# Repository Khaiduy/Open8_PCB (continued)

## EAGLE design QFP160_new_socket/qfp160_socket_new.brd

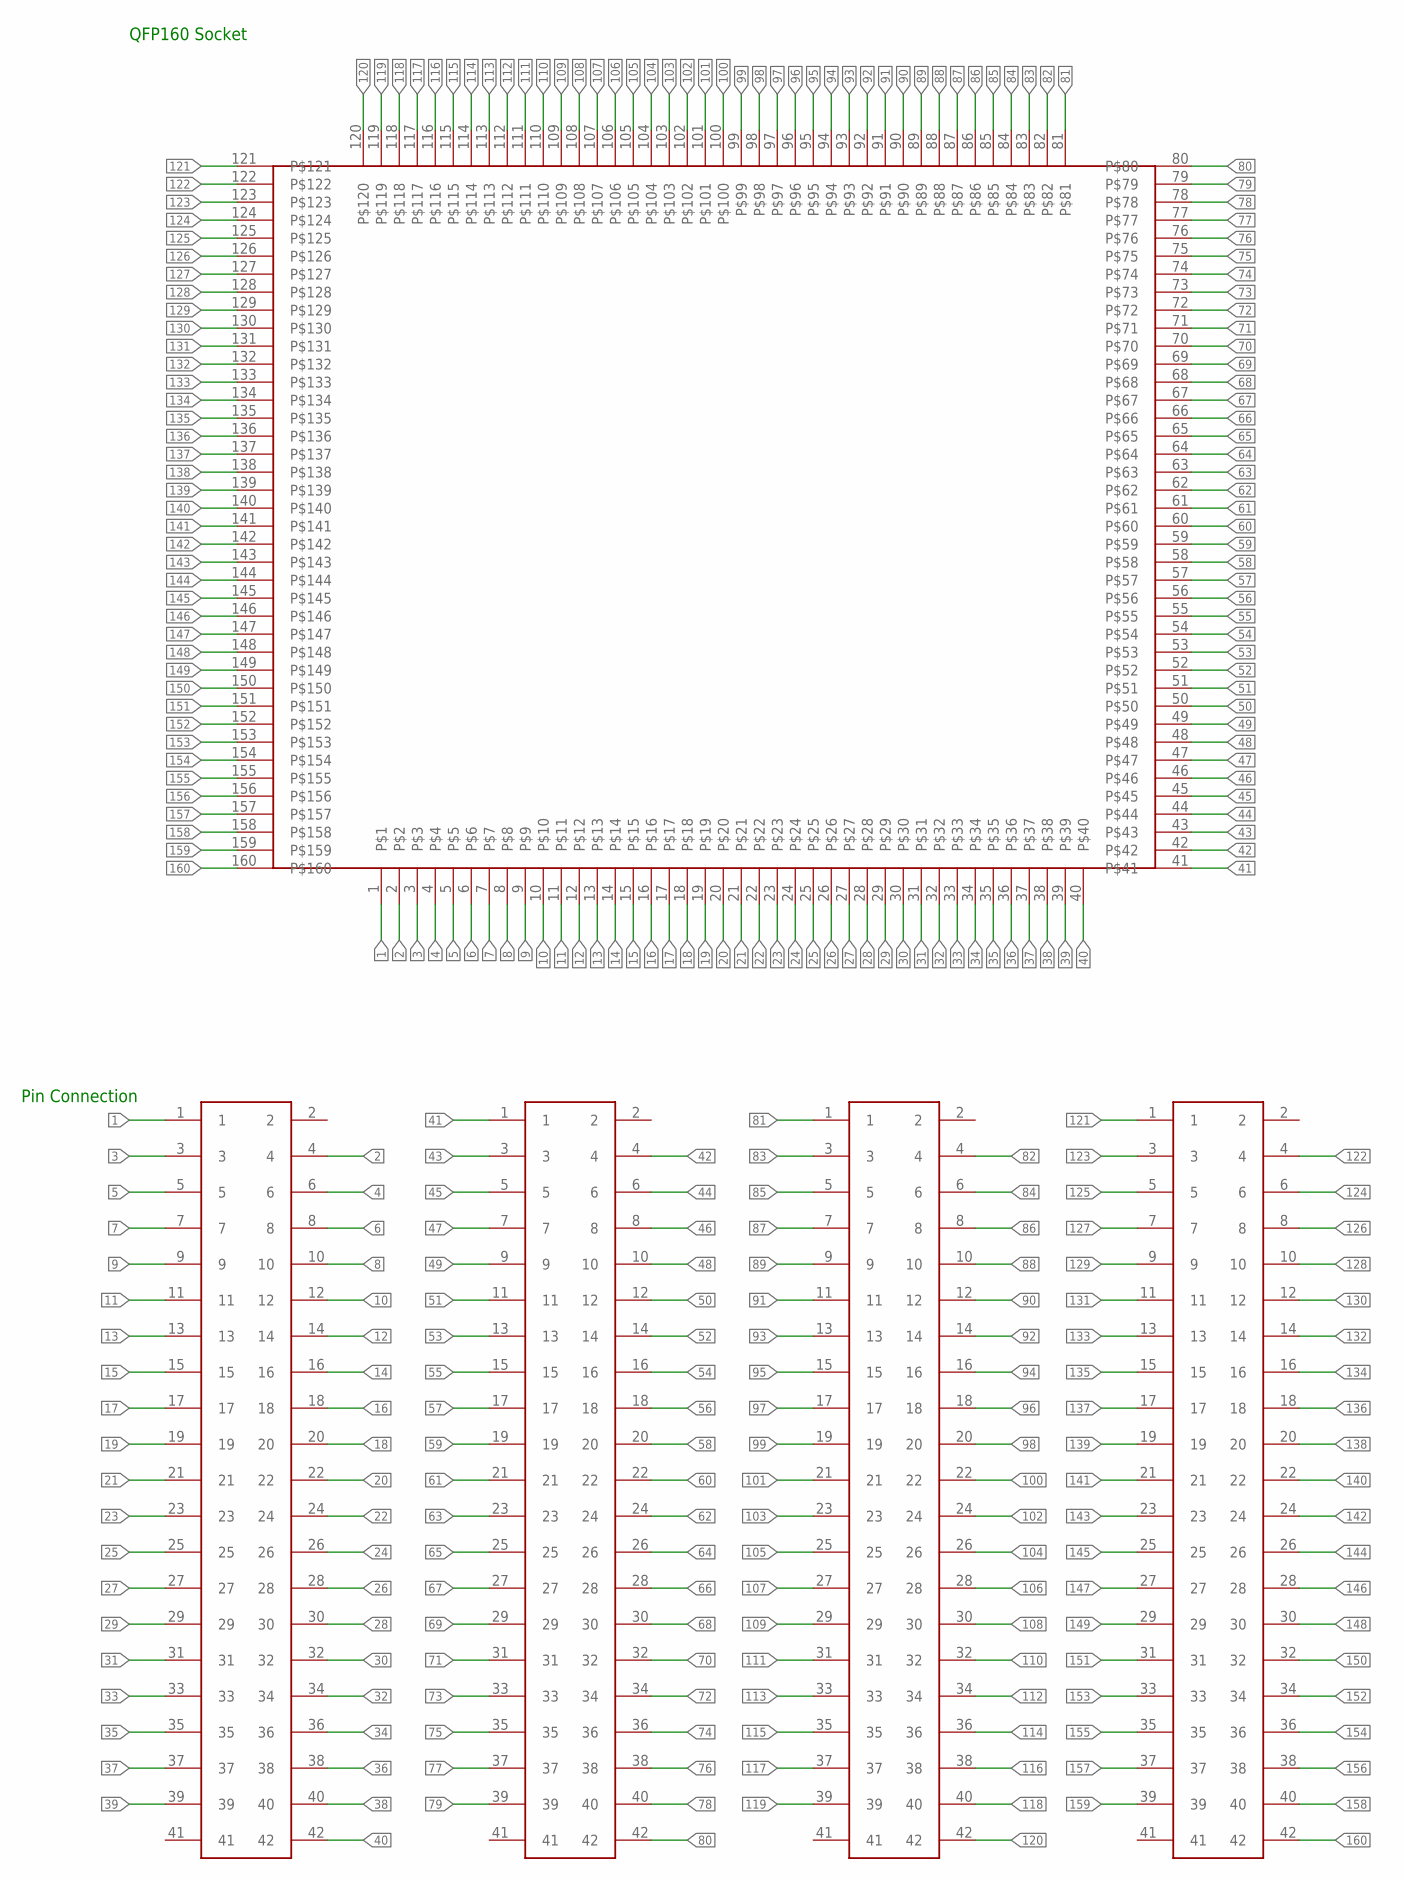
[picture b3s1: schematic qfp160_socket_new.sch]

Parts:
U$1, U$2, U$3, U$4: 2X41_HEADER
U$5: QFP160_SOCKET

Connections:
1: U$1.1, U$5.1
2: U$1.4, U$5.2
3: U$1.3, U$5.3
4: U$1.6, U$5.4
5: U$1.5, U$5.5
6: U$1.8, U$5.6
7: U$1.7, U$5.7
8: U$1.10, U$5.8
9: U$1.9, U$5.9
10: U$1.12, U$5.10
11: U$1.11, U$5.11
12: U$1.14, U$5.12
13: U$1.13, U$5.13
14: U$1.16, U$5.14
15: U$1.15, U$5.15
16: U$1.18, U$5.16
17: U$1.17, U$5.17
18: U$1.20, U$5.18
19: U$1.19, U$5.19
20: U$1.22, U$5.20
21: U$1.21, U$5.21
22: U$1.24, U$5.22
23: U$1.23, U$5.23
24: U$1.26, U$5.24
25: U$1.25, U$5.25
26: U$1.28, U$5.26
27: U$1.27, U$5.27
28: U$1.30, U$5.28
29: U$1.29, U$5.29
30: U$1.32, U$5.30
31: U$1.31, U$5.31
32: U$1.34, U$5.32
33: U$1.33, U$5.33
34: U$1.36, U$5.34
35: U$1.35, U$5.35
36: U$1.38, U$5.36
37: U$1.37, U$5.37
38: U$1.40, U$5.38
39: U$1.39, U$5.39
40: U$1.42, U$5.40
41: U$2.1, U$5.41
42: U$2.4, U$5.42
43: U$2.3, U$5.43
44: U$2.6, U$5.44
45: U$2.5, U$5.45
46: U$2.8, U$5.46
47: U$2.7, U$5.47
48: U$2.10, U$5.48
49: U$2.9, U$5.49
50: U$2.12, U$5.50
51: U$2.11, U$5.51
52: U$2.14, U$5.52
53: U$2.13, U$5.53
54: U$2.16, U$5.54
55: U$2.15, U$5.55
56: U$2.18, U$5.56
57: U$2.17, U$5.57
58: U$2.20, U$5.58
59: U$2.19, U$5.59
60: U$2.22, U$5.60
61: U$2.21, U$5.61
62: U$2.24, U$5.62
63: U$2.23, U$5.63
64: U$2.26, U$5.64
65: U$2.25, U$5.65
66: U$2.28, U$5.66
67: U$2.27, U$5.67
68: U$2.30, U$5.68
69: U$2.29, U$5.69
70: U$2.32, U$5.70
71: U$2.31, U$5.71
72: U$2.34, U$5.72
73: U$2.33, U$5.73
74: U$2.36, U$5.74
75: U$2.35, U$5.75
76: U$2.38, U$5.76
77: U$2.37, U$5.77
78: U$2.40, U$5.78
79: U$2.39, U$5.79
80: U$2.42, U$5.80
81: U$3.1, U$5.81
82: U$3.4, U$5.82
83: U$3.3, U$5.83
84: U$3.6, U$5.84
85: U$3.5, U$5.85
86: U$3.8, U$5.86
87: U$3.7, U$5.87
88: U$3.10, U$5.88
89: U$3.9, U$5.89
90: U$3.12, U$5.90
91: U$3.11, U$5.91
92: U$3.14, U$5.92
93: U$3.13, U$5.93
94: U$3.16, U$5.94
95: U$3.15, U$5.95
96: U$3.18, U$5.96
97: U$3.17, U$5.97
98: U$3.20, U$5.98
99: U$3.19, U$5.99
100: U$3.22, U$5.100
101: U$3.21, U$5.101
102: U$3.24, U$5.102
103: U$3.23, U$5.103
104: U$3.26, U$5.104
105: U$3.25, U$5.105
106: U$3.28, U$5.106
107: U$3.27, U$5.107
108: U$3.30, U$5.108
109: U$3.29, U$5.109
110: U$3.32, U$5.110
111: U$3.31, U$5.111
112: U$3.34, U$5.112
113: U$3.33, U$5.113
114: U$3.36, U$5.114
115: U$3.35, U$5.115
116: U$3.38, U$5.116
117: U$3.37, U$5.117
118: U$3.40, U$5.118
119: U$3.39, U$5.119
120: U$3.42, U$5.120
121: U$4.1, U$5.121
122: U$4.4, U$5.122
123: U$4.3, U$5.123
124: U$4.6, U$5.124
125: U$4.5, U$5.125
126: U$4.8, U$5.126
127: U$4.7, U$5.127
128: U$4.10, U$5.128
129: U$4.9, U$5.129
130: U$4.12, U$5.130
131: U$4.11, U$5.131
132: U$4.14, U$5.132
133: U$4.13, U$5.133
134: U$4.16, U$5.134
135: U$4.15, U$5.135
136: U$4.18, U$5.136
137: U$4.17, U$5.137
138: U$4.20, U$5.138
139: U$4.19, U$5.139
140: U$4.22, U$5.140
141: U$4.21, U$5.141
142: U$4.24, U$5.142
143: U$4.23, U$5.143
144: U$4.26, U$5.144
145: U$4.25, U$5.145
146: U$4.28, U$5.146
147: U$4.27, U$5.147
148: U$4.30, U$5.148
149: U$4.29, U$5.149
150: U$4.32, U$5.150
151: U$4.31, U$5.151
152: U$4.34, U$5.152
153: U$4.33, U$5.153
154: U$4.36, U$5.154
155: U$4.35, U$5.155
156: U$4.38, U$5.156
157: U$4.37, U$5.157
158: U$4.40, U$5.158
159: U$4.39, U$5.159
160: U$4.42, U$5.160

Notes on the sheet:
QFP160 Socket
Pin Connection

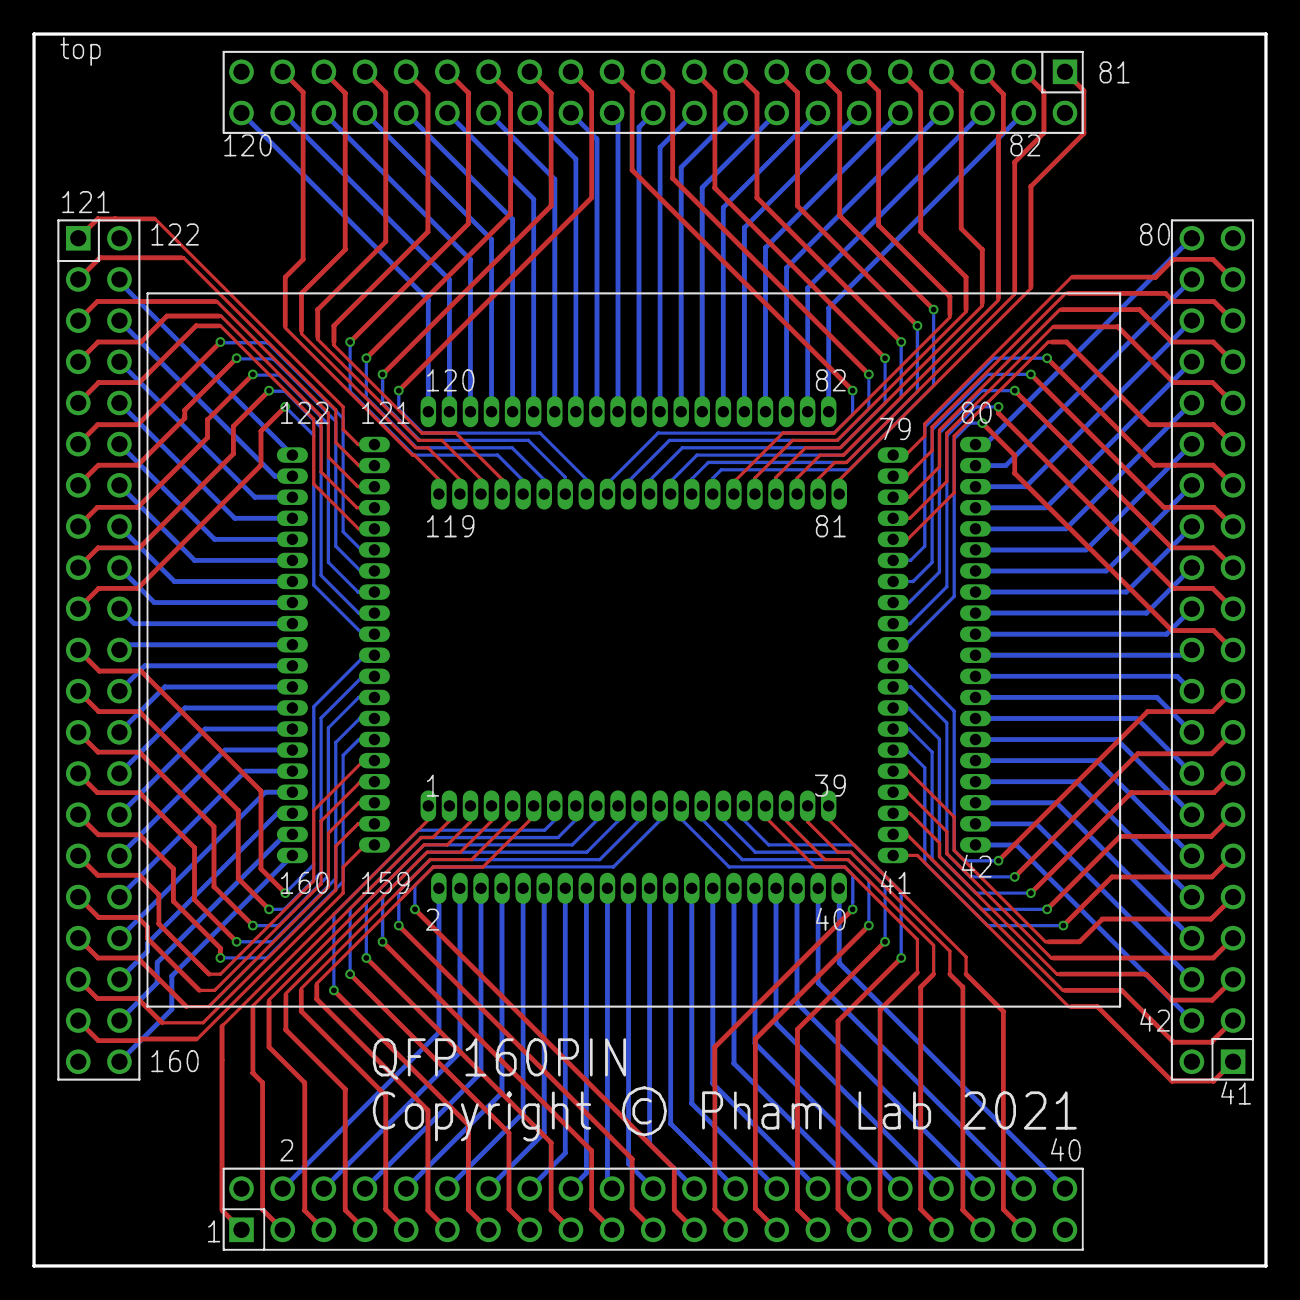
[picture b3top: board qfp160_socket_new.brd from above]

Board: 2 copper layers, 76.0 x 76.0 mm, 5 parts (0 on the bottom side), 160 nets.

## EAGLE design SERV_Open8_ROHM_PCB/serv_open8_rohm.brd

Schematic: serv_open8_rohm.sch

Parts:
C1, C3, C5, C6, C9, C11: 1.0uF; 0603
C2, C4, C7, C8, C10, C12: 4.7uF; 0603
C13, C14, C16, C19, C21, C23, C29, C30, C31, C32, C34, C35, C36, C37, C38, C39, C40, C41, C42, C43, C44: 0.1uF; 0603
C15, C17, C18, C20, C24: 10uF; 0603
C25, C26: 36pF; 0603
C27, C28: 22pF; 0603
CLOCK: PINHD-2X3; 2X03
D1, D2, D3, D4, D5, D19, D20, D21, D22: LED0; LED-0603
FLASH_OPEN8: PINHD-2X6; 2X06
FLASH_SERV: PINHD-2X6; 2X06
GND: PINHD-2X3; 2X03
H1, H2, H3, H4: MOUNT-HOLE3.3; 3,3
IC1, IC2: SN74LVC1GU04DBVR; SOT95P280X145-5N
IC3, IC4, IC5, IC6, IC7, IC8, IC10, IC11: TXB0108PWR; SOP65P640X120-20N
IN_3V3: REG_IN_IO; JP1
IN_OPEN8: REG_IN_OPEN8; JP1
IN_RAM: REG_IN_OPEN8; JP1
IN_SERV: REG_IN_SERV; JP1
IN_VDD: REG_IN; JP1
IN_VDDO: REG_IN_SERV; JP1
J4: 2985-6004; 29856004
JTAG_OPEN8: PINHD-2X10; 2X10
JTAG_SERV: PINHD-2X10; 2X10
LORA_OPEN8: RFM95W-915S2; RFM95-915S2
LORA_SERV: RFM95W-915S2; RFM95-915S2
MUX: PINHD-1X2; 1X02
NRESET_OPEN8: REG_IN; JP1
NRESET_SERV: REG_IN; JP1
OPEN8_FLASH, OPEN8_LORA, OPEN8_SPI: PINHD-2X4; 2X04
OPEN8_JTAG: PINHD-2X5; 2X05
OPEN8_LED: PINHD-1X2; 1X02
OPEN8_SW, OPEN8_UART: PINHD-2X2; 2X02
POWER: PINHD-2X6; 2X06
Q1, Q2, Q3, Q4, Q5, Q16, Q17, Q18, Q19: BSH103,235; SOT95P230X110-3N
R1, R4, R7, R11, R13, R16: 66.5KOHM-0603-1/10W-5%; 0603
R2, R5, R8, R12, R14, R17: 1; 0603
R3, R6, R15, R18, R19: 113k; 0603
R9: 3k; 0603
R10: 243k; 0603
R20, R22, R40, R52, R56, R62, R64, R77, R79: 330; 0603
R21, R23, R32, R33, R34, R39, R41, R48, R53, R54, R55, R57, R63, R65, R78, R80: 10k; 0603
R24, R28: 10M; 0603
R25, R26, R29, R30: 47k; 0603
R27: 2k; 0603
R31: 300k; 0603
S1, S2, S3, S4, S5, S6: SS12SDP2
SERV_FLASH: PINHD-2X4; 2X04
SERV_JTAG: PINHD-2X5; 2X05
SERV_LED: PINHD-1X2; 1X02
SERV_LORA: PINHD-2X4; 2X04
SERV_SPI: PINHD-2X4; 2X04
SERV_SW: PINHD-2X2; 2X02
SERV_UART: PINHD-2X2; 2X02
SPI_OPEN8_1: SPI1; FE10
SPI_OPEN8_2: SPI0; FE10
SPI_SERV_1: SPI0; FE10
SPI_SERV_2: SPI1; FE10
U1, U2, U3, U4, U5, U6: TPS76201DBVR; SOT95P280X145-5N
U$1, U$2, U$3, U$4: 2X41_HEADER
USB-UART_OPEN8_1, USB-UART_OPEN8_2: PINHD-1X4; 1X04
USB-UART_SERV_1, USB-UART_SERV_2: PINHD-1X4; 1X04
Y2: HC-49SM8MHZ20PF30PPM; HC49SM8MHZ20PF30PPM
Y3: Q13FC1350000400

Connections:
1: U$1.1
2: U$1.4
4: U$1.6
5: U$1.5
6: U$1.8
7: U$1.7
8: U$1.10
8MHZ_CLOCK: CLOCK.3, IC1.4 (Y), R24.2, R27.2
9: U$1.9
10: U$1.12
11: U$1.11
12: U$1.14
14: U$1.16
15: U$1.15
16: U$1.18
17: U$1.17
18: U$1.20
19: U$1.19
20: U$1.22
21: U$1.21
22: U$1.24
23: U$1.23
24: U$1.26
25: U$1.25
26: U$1.28
28: U$1.30
29: U$1.29
30: U$1.32
31: U$1.31
32: U$1.34
32KHZ_CLOCK: CLOCK.1, IC2.4 (Y), R28.2, R31.2
33: U$1.33
34: U$1.36
35: U$1.35
36: U$1.38
38: U$1.40
39: U$1.39
40: U$1.42
41: U$2.1
42: U$2.4
44: U$2.6
45: U$2.5
46: U$2.8
47: U$2.7
48: U$2.10
49: U$2.9
50: U$2.12
51: U$2.11
52: U$2.14
54: U$2.16
55: U$2.15
56: U$2.18
57: U$2.17
58: U$2.20
59: U$2.19
60: U$2.22
67: U$2.27
78: U$2.40
79: U$2.39
80: U$2.42
81: U$3.1
82: U$3.4
84: U$3.6
93: U$3.13
107: U$3.27
118: U$3.40
119: U$3.39
120: U$3.42
121: U$4.1
122: U$4.4
124: U$4.6
135: U$4.15
139: U$4.19
140: U$4.22
141: U$4.21
142: U$4.24
143: U$4.23
144: U$4.26
145: U$4.25
146: U$4.28
148: U$4.30
149: U$4.29
150: U$4.32
151: U$4.31
152: U$4.34
153: U$4.33
154: U$4.36
155: U$4.35
156: U$4.38
158: U$4.40
159: U$4.39
160: U$4.42
DR_CLOCK: CLOCK.2, CLOCK.4, CLOCK.6, U$2.28
DR_MUX: MUX.1, R34.2, U$3.23
DR_OPEN8_DIPSW_0: OPEN8_SW.1, U$3.11
DR_OPEN8_DIPSW_1: OPEN8_SW.3, U$3.14
DR_OPEN8_JTAG_TCK: OPEN8_JTAG.7, U$2.38
DR_OPEN8_JTAG_TDI: OPEN8_JTAG.1, U$3.5
DR_OPEN8_JTAG_TDO: OPEN8_JTAG.3, U$3.8
DR_OPEN8_JTAG_TMS: OPEN8_JTAG.9, U$2.35
DR_OPEN8_JTAG_TRST: OPEN8_JTAG.5, U$3.18
DR_OPEN8_LED_0: OPEN8_LED.1, U$3.7
DR_OPEN8_PSPI_CS: OPEN8_SPI.3, U$3.19
DR_OPEN8_PSPI_MISO: OPEN8_SPI.7, U$3.17
DR_OPEN8_PSPI_MOSI: OPEN8_SPI.5, U$3.20
DR_OPEN8_PSPI_SCK: OPEN8_SPI.1, U$3.22
DR_OPEN8_RESET: NRESET_OPEN8.1, U$2.30
DR_OPEN8_SPIFLASH_CIPO: OPEN8_FLASH.1, U$3.16
DR_OPEN8_SPIFLASH_COPI: OPEN8_FLASH.5, U$3.9
DR_OPEN8_SPIFLASH_CS: OPEN8_FLASH.3, U$3.12
DR_OPEN8_SPIFLASH_SCK: OPEN8_FLASH.7, U$3.10
DR_OPEN8_SPI_CS: OPEN8_LORA.3, U$2.33
DR_OPEN8_SPI_MISO: OPEN8_LORA.7, U$2.31
DR_OPEN8_SPI_MOSI: OPEN8_LORA.5, U$2.34
DR_OPEN8_SPI_SCK: OPEN8_LORA.1, U$2.36
DR_OPEN8_UART_RXD: OPEN8_UART.3, U$2.29
DR_OPEN8_UART_TXD: OPEN8_UART.1, U$2.32
DR_OPEN8_VDD: C13.1, C18.1, POWER.10, Q16.1 (G), R63.2, U$2.23
DR_RAM_VDD: C23.1, C24.1, POWER.12, Q2.1 (G), R23.2, U$2.21
DR_SERV_DIPSW_0: SERV_SW.1, U$4.9
DR_SERV_DIPSW_1: SERV_SW.3, U$4.12
DR_SERV_JTAG_TCK: SERV_JTAG.7, U$3.36
DR_SERV_JTAG_TDI: SERV_JTAG.5, U$3.35
DR_SERV_JTAG_TDO: SERV_JTAG.3, U$3.38
DR_SERV_JTAG_TMS: SERV_JTAG.9, U$3.33
DR_SERV_JTAG_TRST: SERV_JTAG.1, U$4.14
DR_SERV_LED_0: SERV_LED.1, U$4.5
DR_SERV_PSPI_CS: SERV_SPI.3, U$4.17
DR_SERV_PSPI_MISO: SERV_SPI.7, U$4.16
DR_SERV_PSPI_MOSI: SERV_SPI.5, U$4.18
DR_SERV_PSPI_SCK: SERV_SPI.1, U$4.20
DR_SERV_RESET: NRESET_SERV.1, U$3.26
DR_SERV_SPIFLASH_CIPO: SERV_FLASH.1, U$4.11
DR_SERV_SPIFLASH_COPI: SERV_FLASH.5, U$4.7
DR_SERV_SPIFLASH_CS: SERV_FLASH.3, U$4.8
DR_SERV_SPIFLASH_SCK: SERV_FLASH.7, U$4.10
DR_SERV_SPI_CS: SERV_LORA.3, U$3.31
DR_SERV_SPI_MISO: SERV_LORA.7, U$3.29
DR_SERV_SPI_MOSI: SERV_LORA.5, U$3.32
DR_SERV_SPI_SCK: SERV_LORA.1, U$3.34
DR_SERV_UART_RXD: SERV_UART.1, U$3.28
DR_SERV_UART_TXD: SERV_UART.3, U$3.30
DR_SERV_VDD: C14.1, C15.1, POWER.8, Q17.1 (G), R65.2, U$3.21
GND: C1.2, C3.2, C5.2, C6.2, C9.2, C11.2, C13.2, C14.2, C15.2, C16.2, C17.2, C18.2, C19.2, C20.2, C21.2, C23.2, C24.2, C25.2, C26.1, C27.2, C28.1, C29.2, C30.2, C31.2, C32.2, C34.2, C35.2, C36.2, C37.2, C38.2, C39.2, C40.2, C41.2, C42.2, C43.2, C44.2, FLASH_OPEN8.3, FLASH_OPEN8.4, FLASH_SERV.3, FLASH_SERV.4, GND.1, GND.2, GND.3, GND.4, GND.5, GND.6, IC3.11 (GND), IC4.11 (GND), IC5.11 (GND), IC6.11 (GND), IC7.11 (GND), IC8.11 (GND), IC10.11 (GND), IC11.11 (GND), J4.1, J4.2, J4.3, J4.4, JTAG_OPEN8.4, JTAG_OPEN8.6, JTAG_OPEN8.8, JTAG_OPEN8.10, JTAG_OPEN8.12, JTAG_OPEN8.14, JTAG_OPEN8.16, JTAG_OPEN8.18, JTAG_OPEN8.20, JTAG_SERV.4, JTAG_SERV.6, JTAG_SERV.8, JTAG_SERV.10, JTAG_SERV.12, JTAG_SERV.14, JTAG_SERV.16, JTAG_SERV.18, JTAG_SERV.20, LORA_OPEN8.P$1 (GND_1), LORA_OPEN8.P$8 (GND_2), LORA_OPEN8.P$15 (GND_3), LORA_SERV.P$1 (GND_1), LORA_SERV.P$8 (GND_2), LORA_SERV.P$15 (GND_3), MUX.2, Q1.2 (S), Q2.2 (S), Q3.2 (S), Q4.2 (S), Q5.2 (S), Q16.2 (S), Q17.2 (S), Q18.2 (S), Q19.2 (S), R1.1, R2.1, R4.1, R5.1, R7.1, R8.1, R11.1, R12.1, R13.1, R14.1, R16.1, R17.1, R21.1, R23.1, R26.1, R30.1, R48.1, R53.1, R57.1, R63.1, R65.1, R78.1, R80.1, S1.3 (ON_2), S2.3 (ON_2), S3.3 (ON_2), S4.3 (ON_2), S5.3 (ON_2), S6.3 (ON_2), SPI_OPEN8_2.10, SPI_SERV_1.10, U1.2 (GND), U1.3 (!EN), U2.2 (GND), U2.3 (!EN), U3.2 (GND), U3.3 (!EN), U4.2 (GND), U4.3 (!EN), U5.2 (GND), U5.3 (!EN), U6.2 (GND), U6.3 (!EN), U$1.3, U$1.37, U$2.3, U$2.24, U$2.26, U$2.37, U$3.3, U$3.24, U$3.37, U$4.3, U$4.37, USB-UART_OPEN8_1.1, USB-UART_SERV_1.1
IN_3V3: C3.1, IN_3V3.2, U2.1 (IN)
IN_OPEN8: C6.1, IN_OPEN8.2, U4.1 (IN)
IN_RAM: C9.1, IN_RAM.2, U5.1 (IN)
IN_SERV: C1.1, IN_SERV.2, U1.1 (IN)
IN_VDD: C5.1, IN_VDD.2, U3.1 (IN)
IN_VDDO: C11.1, IN_VDDO.2, U6.1 (IN)
unnamed: R1.2, R3.1, U1.4 (FB)
unnamed: C2.2, R2.2
unnamed: R4.2, R6.1, U5.4 (FB)
unnamed: C10.2, R5.2
unnamed: R11.2, R18.1, U6.4 (FB)
unnamed: R7.2, R10.1, U2.4 (FB)
unnamed: C4.2, R8.2
unnamed: R9.1, R10.2
unnamed: C12.2, R12.2
unnamed: D1.A, R20.1
unnamed: D1.C, Q1.3 (D)
unnamed: R13.2, R19.1, U3.4 (FB)
unnamed: C8.2, R14.2
unnamed: D2.A, R22.1
unnamed: D2.C, Q2.3 (D)
unnamed: IC1.3 (GND), R26.2
unnamed: C25.1, IC1.2 (A), R24.1, Y2.2 (CRYSTAL_2)
unnamed: C26.2, R27.1, Y2.1 (CRYSTAL_1)
unnamed: IC1.5 (VCC), R25.1
unnamed: IC3.3 (A2), OPEN8_LORA.2
unnamed: R32.1, S1.1 (ON_1)
unnamed: R33.1, S2.1 (ON_1)
unnamed: NRESET_OPEN8.2, S1.2 (COM)
unnamed: NRESET_SERV.2, S2.2 (COM)
unnamed: IC3.4 (A3), OPEN8_LORA.4
unnamed: IC3.5 (A4), OPEN8_LORA.6
unnamed: IC3.6 (A5), OPEN8_LORA.8
unnamed: IC4.3 (A2), OPEN8_FLASH.2
unnamed: R15.1, R16.2, U4.4 (FB)
unnamed: IC2.3 (GND), R30.2
unnamed: C7.2, R17.2
unnamed: C27.1, IC2.2 (A), R28.1, Y3.2 (CRYSTAL_2)
unnamed: C28.2, R31.1, Y3.1 (CRYSTAL_1)
unnamed: IC4.4 (A3), OPEN8_FLASH.4
unnamed: IC2.5 (VCC), R29.1
unnamed: IC4.5 (A4), OPEN8_FLASH.6
unnamed: IC4.6 (A5), OPEN8_FLASH.8
unnamed: IC11.4 (A3), OPEN8_SPI.2
unnamed: IC11.5 (A4), OPEN8_SPI.4
unnamed: IC11.6 (A5), OPEN8_SPI.6
unnamed: IC11.7 (A6), OPEN8_SPI.8
unnamed: R41.1, S4.1 (ON_1)
unnamed: D4.A, R40.1
unnamed: D4.C, Q3.3 (D)
unnamed: OPEN8_SW.4, S4.2 (COM)
unnamed: R39.1, S3.1 (ON_1)
unnamed: OPEN8_SW.2, S3.2 (COM)
unnamed: IC6.1 (A1), OPEN8_JTAG.2
unnamed: IC6.3 (A2), OPEN8_JTAG.4
unnamed: IC6.4 (A3), OPEN8_JTAG.6
unnamed: IC6.5 (A4), OPEN8_JTAG.8
unnamed: IC6.6 (A5), OPEN8_JTAG.10
unnamed: IC6.7 (A6), OPEN8_UART.2
unnamed: IC6.8 (A7), OPEN8_UART.4
unnamed: IC5.3 (A2), SERV_LORA.2
unnamed: IC5.4 (A3), SERV_LORA.4
unnamed: D19.A, R62.1
unnamed: IC5.5 (A4), SERV_LORA.6
unnamed: IC5.6 (A5), SERV_LORA.8
unnamed: IC7.3 (A2), SERV_FLASH.2
unnamed: IC7.4 (A3), SERV_FLASH.4
unnamed: IC7.5 (A4), SERV_FLASH.6
unnamed: IC7.6 (A5), SERV_FLASH.8
unnamed: D19.C, Q16.3 (D)
unnamed: D20.A, R64.1
unnamed: D20.C, Q17.3 (D)
unnamed: D21.A, R77.1
unnamed: D21.C, Q18.3 (D)
unnamed: D22.A, R79.1
unnamed: D22.C, Q19.3 (D)
unnamed: IC8.3 (A2), SERV_SPI.2
unnamed: IC8.4 (A3), SERV_SPI.4
unnamed: IC8.5 (A4), SERV_SPI.6
unnamed: IC8.6 (A5), SERV_SPI.8
unnamed: IC10.1 (A1), SERV_JTAG.2
unnamed: IC10.3 (A2), SERV_JTAG.4
unnamed: IC10.4 (A3), SERV_JTAG.6
unnamed: IC10.5 (A4), SERV_JTAG.8
unnamed: IC10.6 (A5), SERV_JTAG.10
unnamed: IC10.7 (A6), SERV_UART.2
unnamed: IC10.8 (A7), SERV_UART.4
unnamed: D3.A, R52.1
unnamed: D3.C, Q4.3 (D)
unnamed: R54.1, S5.1 (ON_1)
unnamed: S5.2 (COM), SERV_SW.2
unnamed: R55.1, S6.1 (ON_1)
unnamed: S6.2 (COM), SERV_SW.4
unnamed: D5.A, R56.1
unnamed: D5.C, Q5.3 (D)
OPEN8_FLASH_CIPO: FLASH_OPEN8.8, IC4.18 (B2)
OPEN8_FLASH_COPI: FLASH_OPEN8.10, IC4.16 (B4)
OPEN8_FLASH_CS: FLASH_OPEN8.12, IC4.17 (B3)
OPEN8_FLASH_SCK: FLASH_OPEN8.6, IC4.15 (B5)
OPEN8_JTAG_TCK: IC6.16 (B4), JTAG_OPEN8.9
OPEN8_JTAG_TDI: IC6.20 (B1), JTAG_OPEN8.5
OPEN8_JTAG_TDO: IC6.18 (B2), JTAG_OPEN8.13
OPEN8_JTAG_TMS: IC6.15 (B5), JTAG_OPEN8.7
OPEN8_JTAG_TRST: IC6.17 (B3), JTAG_OPEN8.3
OPEN8_LED: OPEN8_LED.2, Q3.1 (G), R48.2
OPEN8_LORA_CS: IC3.17 (B3), LORA_OPEN8.P$5 (NSS)
OPEN8_LORA_MISO: IC3.15 (B5), LORA_OPEN8.P$2 (MISO)
OPEN8_LORA_MOSI: IC3.16 (B4), LORA_OPEN8.P$3 (MOSI)
OPEN8_LORA_SCK: IC3.18 (B2), LORA_OPEN8.P$4 (SCK)
OPEN8_PROG_CS: IC11.16 (B4), SPI_OPEN8_2.4
OPEN8_PROG_MISO: IC11.14 (B6), SPI_OPEN8_2.3
OPEN8_PROG_MOSI: IC11.15 (B5), SPI_OPEN8_2.2
OPEN8_PROG_SCK: IC11.17 (B3), SPI_OPEN8_2.1
OPEN8_UART_RX: IC6.13 (B7), USB-UART_OPEN8_1.2
OPEN8_UART_TX: IC6.14 (B6), USB-UART_OPEN8_1.4
OUT_3V3: C4.1, POWER.1, R9.2, U2.5 (OUT)
OUT_OPEN8: C7.1, POWER.7, R15.2, U4.5 (OUT)
OUT_RAM: C10.1, POWER.11, R6.2, U5.5 (OUT)
OUT_SERV: C2.1, POWER.9, R3.2, U1.5 (OUT)
OUT_VDD: C8.1, POWER.5, R19.2, U3.5 (OUT)
OUT_VDDO: C12.1, POWER.3, R18.2, U6.5 (OUT)
SERV_FLASH_CIPO: FLASH_SERV.8, IC7.18 (B2)
SERV_FLASH_COPI: FLASH_SERV.10, IC7.16 (B4)
SERV_FLASH_CS: FLASH_SERV.12, IC7.17 (B3)
SERV_FLASH_SCK: FLASH_SERV.6, IC7.15 (B5)
SERV_JTAG_TCK: IC10.16 (B4), JTAG_SERV.9
SERV_JTAG_TDI: IC10.17 (B3), JTAG_SERV.5
SERV_JTAG_TDO: IC10.18 (B2), JTAG_SERV.13
SERV_JTAG_TMS: IC10.15 (B5), JTAG_SERV.7
SERV_JTAG_TRST: IC10.20 (B1), JTAG_SERV.3
SERV_LED: Q4.1 (G), R53.2, SERV_LED.2
SERV_LORA_CS: IC5.17 (B3), LORA_SERV.P$5 (NSS)
SERV_LORA_MISO: IC5.15 (B5), LORA_SERV.P$2 (MISO)
SERV_LORA_MOSI: IC5.16 (B4), LORA_SERV.P$3 (MOSI)
SERV_LORA_SCK: IC5.18 (B2), LORA_SERV.P$4 (SCK)
SERV_PROG_CS: IC8.17 (B3), SPI_SERV_1.4
SERV_PROG_MISO: IC8.15 (B5), SPI_SERV_1.3
SERV_PROG_MOSI: IC8.16 (B4), SPI_SERV_1.2
SERV_PROG_SCK: IC8.18 (B2), SPI_SERV_1.1
SERV_UART_RX: IC10.14 (B6), USB-UART_SERV_1.2
SERV_UART_TX: IC10.13 (B7), USB-UART_SERV_1.4
SMA_CLK: CLOCK.5, J4.5
VDD: C19.1, C20.1, POWER.6, Q1.1 (G), R21.2, U$1.13, U$2.13, U$3.15, U$4.13
VDDO: C16.1, C17.1, C30.1, C32.1, C34.1, C35.1, C38.1, C40.1, C42.1, C43.1, IC3.2 (VCCA), IC3.10 (OE), IC4.2 (VCCA), IC4.10 (OE), IC5.2 (VCCA), IC5.10 (OE), IC6.2 (VCCA), IC6.10 (OE), IC7.2 (VCCA), IC7.10 (OE), IC8.2 (VCCA), IC8.10 (OE), IC10.2 (VCCA), IC10.10 (OE), IC11.2 (VCCA), IC11.10 (OE), POWER.4, Q19.1 (G), R80.2, U$1.27, U$2.25, U$3.25, U$4.27
VDD_3V3: C21.1, C29.1, C31.1, C36.1, C37.1, C39.1, C41.1, C44.1, FLASH_OPEN8.1, FLASH_OPEN8.2, FLASH_SERV.1, FLASH_SERV.2, IC3.19 (VCCB), IC4.19 (VCCB), IC5.19 (VCCB), IC6.19 (VCCB), IC7.19 (VCCB), IC8.19 (VCCB), IC10.19 (VCCB), IC11.19 (VCCB), JTAG_OPEN8.1, JTAG_OPEN8.2, JTAG_SERV.1, JTAG_SERV.2, LORA_OPEN8.P$12 (3.3V), LORA_SERV.P$12 (3.3V), POWER.2, Q18.1 (G), R20.2, R22.2, R25.2, R29.2, R32.2, R33.2, R34.1, R39.2, R40.2, R41.2, R52.2, R54.2, R55.2, R56.2, R62.2, R64.2, R77.2, R78.2, R79.2, USB-UART_OPEN8_1.3, USB-UART_SERV_1.3
VDD_5V: IN_3V3.1, IN_OPEN8.1, IN_RAM.1, IN_SERV.1, IN_VDD.1, IN_VDDO.1, Q5.1 (G), R57.2, USB-UART_OPEN8_2.2, USB-UART_SERV_2.2

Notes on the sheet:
POWER
CLOCK GENERATOR
RESET
Mounting holes
Pin Connection
OPEN8_LORA
SERV_LORA
OPEN8_FLASH
OPEN8_SPI
OPEN8_JTAG
OPEN8_SWITCH
MUX
OPEN8_LED
32KHZ
8MHZ
SMA
SERV_LED
SERV_SWITCH
SERV_JTAG
SERV_UART
SERV_SPI
SERV_FLASH

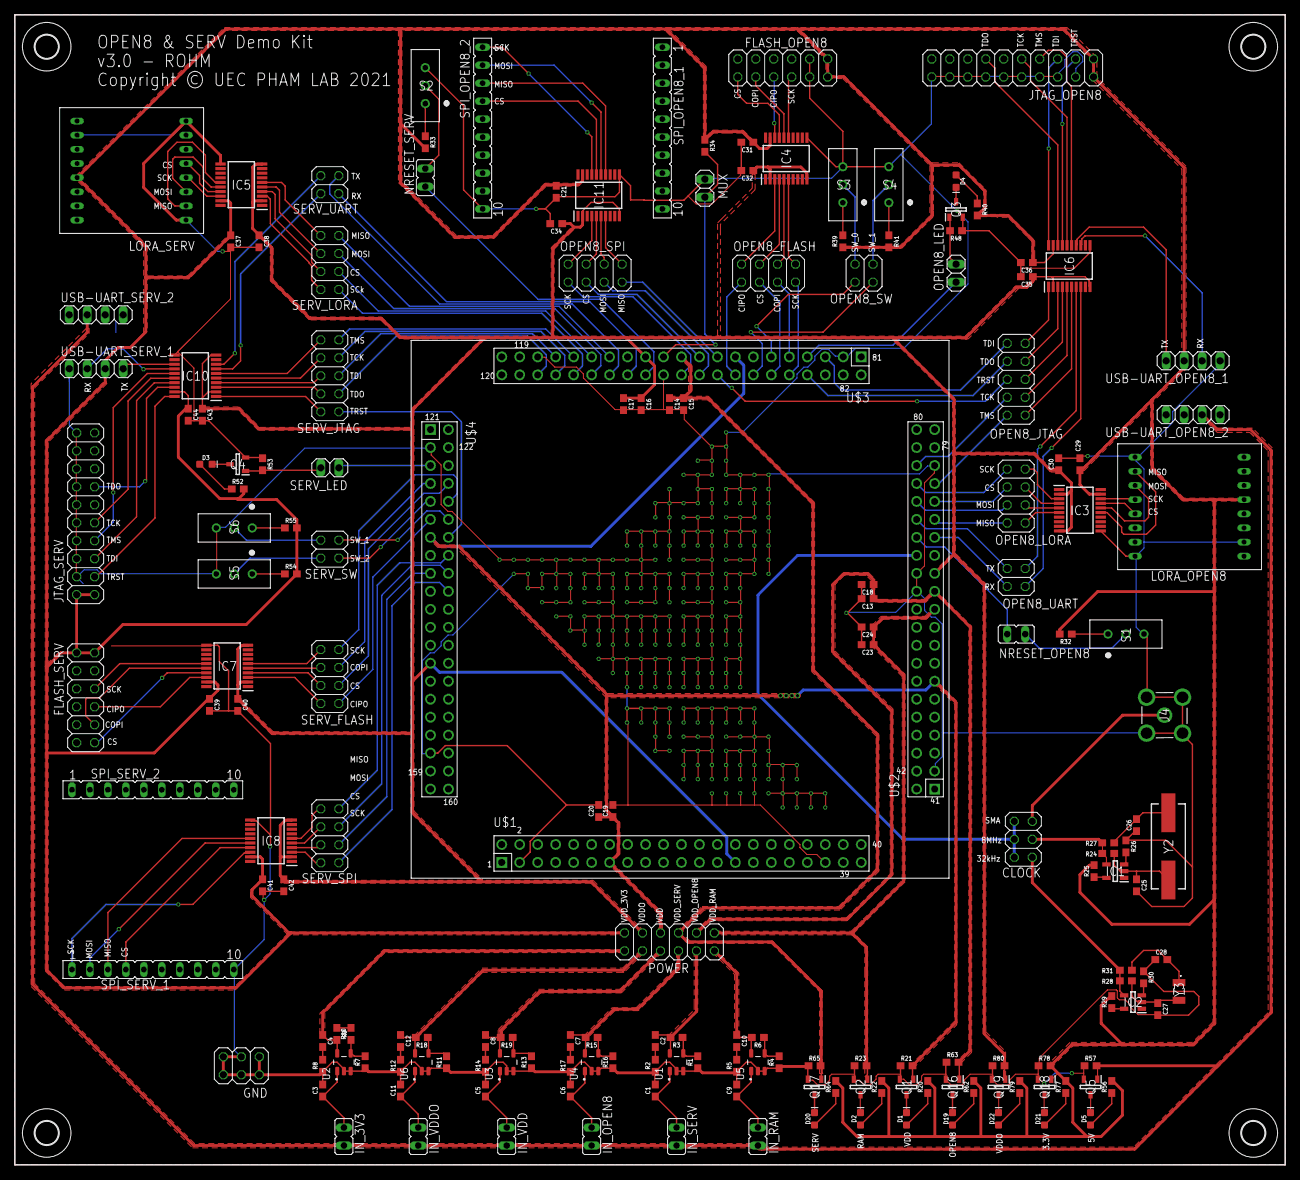
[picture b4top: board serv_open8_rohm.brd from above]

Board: 2 copper layers, 179.5 x 162.5 mm, 185 parts (0 on the bottom side), 200 nets.

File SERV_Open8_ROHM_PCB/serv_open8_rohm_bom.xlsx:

Comment | Designator | Footprint | LCSC Part #（optional）
1 Ohm | R2, R5, R8, R12, R14, R17 | 603 | C247057
0.1uF | C13, C14, C16, C19, C21, C23, C29, C30, C31, C32, C34, C35, C36, C37, C38, C39,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 | 603 | C77055
1.0uF | C1, C3, C5, C6, C9, C11 | 603 | C1689
10MOhm | R24, R28 | 603 | C7250
10k | R21, R23, R32, R33, R34, R39, R41, R48,R53, R54, R55, R57, R63, R65, R78, R80 | 603 | C25804
10uF | C15, C17, C18, C20, C24 | 603 | C85713
113kOhm | R3, R6, R15, R18, R19 | 603 | C22862
22pF | C27, C28 | 603 | C1653
243kOhm | R10 | 603 | C23351
2kOhm | R27 | 603 | C22900
300kOhm | R31 | 603 | C23024
330Ohm | R20, R22, R40, R52, R56, R62, R64, R77, R79 | 603 | C23138
36pF | C25, C26 | 603 | C159790
3kOhm | R9 | 603 | C4211
4.7uF | C2, C4, C7, C8, C10, C12 | 603 | C19666
47kOhm | R25, R26, R29, R30 | 603 | C25819
66.5KOHM | R1, R4, R7, R11, R13, R16 | 603 | C23225
BSH103,235 | Q1, Q2, Q3, Q4, Q5, Q16, Q17, Q18, Q19 | SOT95P230X110-3N | C88711
HC-49SM8MHZ20PF30PPM | Y2 | SMD-CRY-3.8x13.5_2P | C107426
 | D1, D2, D3, D4, D5, D19, D20, D21, D22 | 603 | C2286
Q13FC1350000400 | Y3 | SMD-3215_2P | C32346
SN74LVC1GU04DBVR | IC1, IC2 | SOT-23-5 | C81934
TPS76201DBVR | U1, U2, U3, U4, U5, U6 | SOT-23-5 | C13997
TXB0108PWR | IC3, IC4, IC5, IC6, IC7, IC8, IC10, IC11 | SOP65P640X120 | C53406
